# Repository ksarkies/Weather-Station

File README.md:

Weather Station
---------------

This project aims to produce a weather station consisting of a weatherproofed
processing unit for control and data capture from sensors. This would be
remotely mounted in a suitable location with the sensors and will communicate
with a base station over a serial cable or wirelessly.

The remote unit is ARM Cortex CM3 based and is powered either from the serial
link (if present) and/or from a solar panel with battery backup.

The base station collects and stores data and permit configuration of the
system via a user interface. It consists of a Linux based PC or microcomputer
unit.

Some of the sensors initially are taken from a defunct low cost commercial
weather station. Later they may be replaced with scientific grade sensors.

The sensors to be used are:

1. Temperature and humidity (indoor and outdoor),
2. Wind Speed,
3. Wind Direction,
4. Rainfall,
5. Barometric Pressure,
6. Solar Radiance.

The solar panel provided for power is also used to measure the incident
solar radiance. This is a measure specific to the panel type and is intended
only for providing records of incident radiance for use in design of solar
power generators having similar panel types.

**The battery must be present when the panel is connected**, as high voltages
from the panel can damage the components, and also because the panel is
disconnected from the power circuits during solar irradiance measurements,
which will result in the circuit losing all power.

(c) K. Sarkies 16/08/2017

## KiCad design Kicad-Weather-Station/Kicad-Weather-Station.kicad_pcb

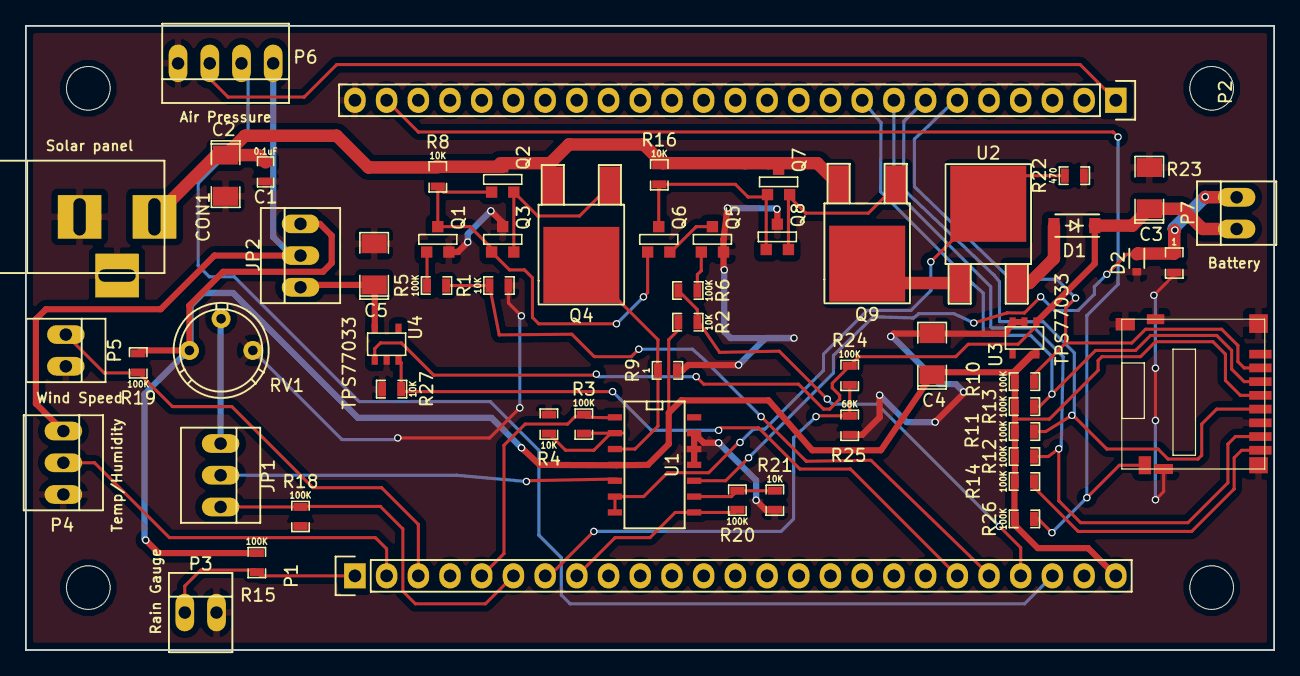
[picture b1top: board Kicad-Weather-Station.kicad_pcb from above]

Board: 2 copper layers, 100.0 x 50.0 mm, 57 parts (0 on the bottom side), 40 nets.

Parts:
C1: 0.1uF; SM0603_Capa
C2, C3: 100uF; SM1206POL
C4, C5: 10uF; SM1206POL
CON1: Solar Panel; BARREL_JACK
D1: MBR0520LT1G; SOD-123
D2: 1N4148; SOD-523
J1: MicroSD; Conn_uSDcard_Amph_114_00841_68
JP1, JP2: JUMPER3; PINHEAD1-3
P1, P2: CONN_01X25; Pin_Header_Straight_1x25
P3: Rain Gauge; PINHEAD1-2
P4: Temperature/Humidity; PINHEAD1-3
P5: Wind Speed; PINHEAD1-2
P6: Air Pressure; PINHEAD1-4
P7: Battery; PINHEAD1-2
Q1, Q2, Q5, Q6, Q7: MMBT3904; SOT23EBC
Q3, Q8: MMBT3906; SOT23EBC
Q4, Q9: SUD45P03-12-GE3; TO-252-2Lead
R1, R2, R4, R8, R16, R21, R27: 10K; SM0603_Resistor
R3, R5, R6, R10, R11, R12, R13, R14, R15, R18, R19, R20, R24, R26: 100K; SM0603_Resistor
R9, R23: 1; SM0603_Resistor
R22: 470; SM0603_Resistor
R25: 68K; SM0603_Resistor
RV1: 100K; Potentiometer_Bourns_3339P_Angular_ScrewUp
U1: LMV324; SOIC-14_N
U2: 78M05; TO-252-2Lead
U3, U4: TPS77033; SOT23-5

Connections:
+3.3V: JP2.2, P4.1, P6.1
+3.3V-M: C4.1, J1.4, JP2.3, P1.25, R2.2, R10.1, R11.1, R12.1, R13.1, R14.1, R15.1, R19.2, R26.1, RV1.1, U1.4, U3.5
Earth: C1.2, C2.2, C3.2, C4.2, C5.2, CON1.2, CON1.3, D2.2, J1.6, J1.12, J1.SHLD, P2.25, P3.2, P4.3, P5.2, P6.4, Q1.1, Q3.3, Q5.1, Q8.3, R1.2, R4.2, R9.2, R18.2, R21.2, R22.2, R23.2, R25.2, R27.2, RV1.3, U1.11, U1.12, U1.13, U3.2, U3.3, U4.2
unnamed: C1.1, C2.1, CON1.1, Q2.3, Q4.3, Q7.3, Q9.3, R8.1, R16.1
unnamed: C5.1, JP2.1, U4.5
unnamed: D1.2, U2.3
unnamed: D2.1, P7.2, R23.1, U1.10
unnamed: JP1.1, RV1.2
unnamed: JP1.2, U1.5
unnamed: Q1.2, R5.1
unnamed: Q1.3, Q2.2, Q3.2, Q6.2, R8.2
unnamed: Q2.1, Q3.1, Q4.1
unnamed: Q4.2, R9.1, U1.3
unnamed: Q5.2, R6.1
unnamed: Q5.3, Q6.1
unnamed: Q6.3, Q7.2, Q8.2, R16.2
unnamed: Q7.1, Q8.1, Q9.1
unnamed: Q9.2, U2.1
unnamed: R3.2, R4.1, U1.2
unnamed: R20.2, R21.1, U1.9
unnamed: R22.1, U1.6, U1.7, U2.2
PA0: P1.1, P3.1, R15.2
PA1: P1.2, P4.2
PA2: P1.3, P5.1, R19.1
PA4: P1.5, R3.1, U1.1
PA5: JP1.3, P1.6, R18.1
PA6: P1.7, R24.2, R25.1
PA7: P1.8, R20.1, U1.8
PB3: P1.20, R27.1, U4.3
PB4: P1.21, R1.1, R5.2
PB5: P1.22, R2.1, R6.2
PB6: P1.23, P6.2
PB7: P2.1, P6.3
PB12: J1.2, P2.6, R10.2
PB13: J1.5, P2.7, R11.2
PB14: J1.7, P2.8, R12.2
PB15: J1.3, P2.9, R13.2
PD2: J1.11, P2.24, R26.2
Power: C3.1, D1.1, P7.1, R24.1, U3.1, U4.1
RSRVD: J1.8, R14.2

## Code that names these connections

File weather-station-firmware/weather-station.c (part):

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This initial development version uses the ET-ARM STAMP board. The port
allocations are:

- PA0: Rainwater gauge. Tipping bucket with reed switch.
- PA1: Temperature and Humidity. Freetronics DHT22.
- PA2: Wind Speed. Reed switch.
- PA3: Wind Direction. Reed switch.
- PA4: Solar Radiance (scale dependent on the panel material).
       Suntech-STP005S12-5W.
- Air Pressure. Freetronics MS-5637-02BA03. I2C-1 on PB6 for SCL, PB7 for SDA.

For battery charging the following are needed:
- PA6 to measure battery voltage on ADC12-IN5.
- PA7 to measure battery current on ADC12-IN6.
- PB2 to switch the panel to charge the battery.
- PB5 to switch the panel to the solar radiance current measurement circuit.

USART1 is on PA8-PA12 with Tx on PA9 and Rx on PA10.

For Memory card SPI interface:
- PD2: for memory card present signal.
- PB12: for memory card select.
- PB13: for memory card SCK.
- PB14: for memory card MISO.
- PB15: for memory card MOSI.

NOTE: The battery must be in place during operation otherwise when the charger
is disabled by the program the processor will power off.

NOTE: the test ET-STM32 STAMP board has a faulty PB4 and PB3.
*/

/*
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
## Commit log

2016-05-07 Add initial files
2016-05-10 Add DHT sensor library from Adafruit Industries, generalised. Not complete or tested.
2016-05-19 Recast DHT.c as C code using a datastructure for the DHT object. hardware.c holds replacement code for the Arduino calls originally used. The low level read/write in DHT.c was changed to generalise t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
2016-05-20 Change from floating point to fixed point arithmetic. Addition of timer and USART functions and flesh out the main test program. Still untested.
2016-05-23 Fixed some bugs that caused the delay loops to hang. Rearrange to place all hardware oriented features into hardware.c along with some utility functions for printout.
2016-05-24 Change timing to set systick to a longer timeout period and compute milliseconds from the systick settings and register values. Add a delaySleep function to sleep until systick timeout interrupt.
2016-06-06 Minor mods to the firmware to get a working test for humidity/temperature.
2016-06-06 First start at mods to barometric sensor code forked from Freetronics. Aim to convert to C code as with the humidity sensor code.
2016-06-06 Schematic for interface board to handle the battery charging and solar panel current measurement. This uses a simple linear regulator plus a D/A output from the processor to limit the battery voltage.
2016-06-07 Update to interface circuit to add battery current measurement.
2016-06-09 Some component changes following testing.
2016-06-12 Add a basic GUI with T and H. Modify firmware to match requirements for CSV communications. Wind direction is omitted until a compass widget can be installed (and a sensor obtained).
2016-06-23 Updates to the firmware to implement A/D conversions and D/A conversion. Some rearrangement of hardware initialization between main file and lib file. Start on i2c needing more work. Not yet imopleme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
2016-06-23 Addition of circuit diagram.
2016-06-24 Complete the EXTI portion. DAC attempted but not working yet. Had to go to ET-STAMP as the ET-STM32F103 dev board failed to activate EXTI if the ADC or Timer2 (sharing pins) were activated. Probably 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
2016-06-27 Add battery charging feature. All A/D conversions now averaged over 16 reads.
2016-07-04 Update to GUI to add all fields from remote. Some not yet scaled.
2016-07-04 More updates to firmware. Change PB4 to PB3 for radiance measurement as the port PB4 on the board benig used is dead.
2016-07-04 Modifications to i2c and further work on barometric sensor code.
2016-07-05 Fix some problems with measurement of currents andmove irradiance switch to PB2 due to faulty hardware.
2016-07-07 Minor updates to the schematics.
2016-07-07 Attempts to get the firmware to put the processor into sleep mode. Works OK for sleep but not yet for stop modes (see next commit).
2016-07-07 A test of the RTC to attempt to put processor to stop mode. Defines an alarm event on EXTI17 which is input for the RTC Alarm event. This works fine for sleep mode but although it wakes from deep sle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
2016-07-13 Fix error in GUI
2016-07-13 Working version of rtc-test. Add makefiles.
2016-07-14 Completion of rtc-test using stop mode, interrupts, RTC alarm wakeup and other EXTI interrupts.
2016-07-14 Simplify code a little
2016-07-15 Style change to loc3 form
2016-07-15 Prettify GUI and add battery health display
2016-07-15 Firmware update to put processor to stop mode using RTC alarm. Add air pressure (sending dummy for now)
2016-07-15 Correct more style errors to kernel C standard.
2016-07-15 Change camelCase to snake_case in firmware
2016-07-16 Fix problem with T and H reading due to systick stopping during sleep. The sensor requires 2 seconds minimum between reads. As systick was stopped, the program thought that not enough time had elapse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
2016-07-16 Move around hardware functions to lib directory. Update some documentation.
2016-07-18 Change T and H measurement to better API with one call to get both.
2016-07-21 GUI changes to UI
2016-07-21 Further work, untested on barometric sensor code.
2016-07-21 Removal of rtc test to ARM-ports project
2016-07-24 First hack at Kicad board for manufacture. Schematic not finished.
2016-07-25 Update to schematics. Kicad version completed with values and annotation.
2016-07-25 Add footprints and create PCB. Some layout started. Trimpot footprint to be defined.
2016-07-26 Initial layout of PCB
2016-07-26 Oops! forgot the microSD card. Rearrangement of PCB layout to accommodate.
2016-07-27 First form of PCB
2016-07-31 Generate Gerbers and images
2016-08-17 Update firmware to start integration of barometric pressure sensor and USART read. For the latter change from deep sleep to light sleep so that the USART interrupt can be recognised.
2016-08-17 Add image of processor portion of prototype circuit and remove PCB.
2016-08-22 Add barometric sensor feature. Based on I2C. Returns T with better accuracy than the humidity sensor. Update GUI to prettify and add a recording header. An odd problem exists in that the constants ob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
2016-08-27 Add Amphenol microSD connector to PCB.
2016-08-27 Add Amphenol microSD connector to PCB and add the CP (card present) signal to PA8.
2016-11-22 Update to PCB and gerbers
2016-11-22 Update to firmware
2016-11-22 Fix deprecated ADC calibration sequence
2016-11-22 Add ChaN FAT directory in preparation for coding file storage.
2017-08-16 Rename some directories
2017-10-11 Firmware: changes to incorporate file recording. Changes to names of various library files Compilation not yet successful for this commite.
2017-10-11 Changes to firmware libraries to underscore naming of functions and removal of all libopencm3 calls into hardware.c
2017-10-12 Further changes to firmware to use common set of functions with underline name format. Correction of error in I2C library. Removal of comms functions from the hardware library. Separation of string f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
2017-10-16 Firmware: move check of incoming messages to the start and isolate deep sleep mode which cannot be used with the USART for receiving messages. Add two delay functions from Data Acquisition (these are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
2017-10-16 GUI: Add record window and code
2017-10-20 Get file recording in firmware to work by moving various functions closer to those used in the data acquisition project. chan_fat is now identical as are the libraries except for hardware.c. The comp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
2017-10-21 Repair code to print fixed point and place in string lib. Add fixed point record to file Combine battery voltage and current to one message as in other projects. Send a time string each message block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
2017-10-21 Add a sensor enable circuit to allow switching of power to sensors that are used only when the processor is awake, to save energy.
2017-10-21 Add in remainder of recording statements.
2017-10-21 Add configure window same as for Data Acquisition. Had to remove reference to RTC in firmware as it was being used for setting and retrieving real time. This must be done through the systick timer as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
2017-10-26 Change to circuit to allow certain peripherals to be powered off during sleep when not required. Peripherals that perform counting are not powered off.
2017-10-26 Minor change to colours of buttons in GUI.
2017-10-26 Add data processing mainly intended at this stage to convert combine records and convert to csv form.
2017-10-27 Change transmission format in firmware to send fixed point as integer (times 256) rather than as floating number. Change GUI and data processing to match.
2017-10-30 Fix problem with measurement cycle at change of time setting. Add change to deep sleep through button press. NOTE: the change back to sleep mode has not yet been achieved apart from a hardware reset.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
2017-11-03 - Add feature to place remote into sleep mode for a few seconds to allow contact by the base station GUI when the remote is in stop mode. This will allow the base station to place remote to sleep mod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
2017-11-03 Fix problem where DAC setting affected pA0 and PA3 rather than PA5
2017-11-14 Corrections to PCB schematic.
2017-11-14 Introduction of header file for firmware.
2017-12-25 Update schematic and PCB to allow some sensors to be powered off.
2018-01-18 Clean up PCB footprints and generate gerbers.
2018-01-19 Regenerate gerbers
2018-02-28 Fix firmware source to refer to the header file. Remove tabs from makefile
2018-05-02 Added missing inversion stage for battery charge MOSFET driver section. Removed clunky earth pin holes and added tracks with vias in the earthing part to ensure that all earths can be connected after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
2018-05-03 Second version of changes to fix MOSFET drivers. Use AND gate form of inverter to ensure that battery charge MOSFET is off when solar panel measurement is on. This does not need any transistors and i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

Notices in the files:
weather-station-firmware/weather-station.c:
This program is free software: you can redistribute it and/or modify
it under the terms of the GNU General Public License as published by
the Free Software Foundation, either version 3 of the License, or
(at your option) any later version.
Kicad-Weather-Station/Kicad-Weather-Station.kicad_pcb:
license cc-by-sa
